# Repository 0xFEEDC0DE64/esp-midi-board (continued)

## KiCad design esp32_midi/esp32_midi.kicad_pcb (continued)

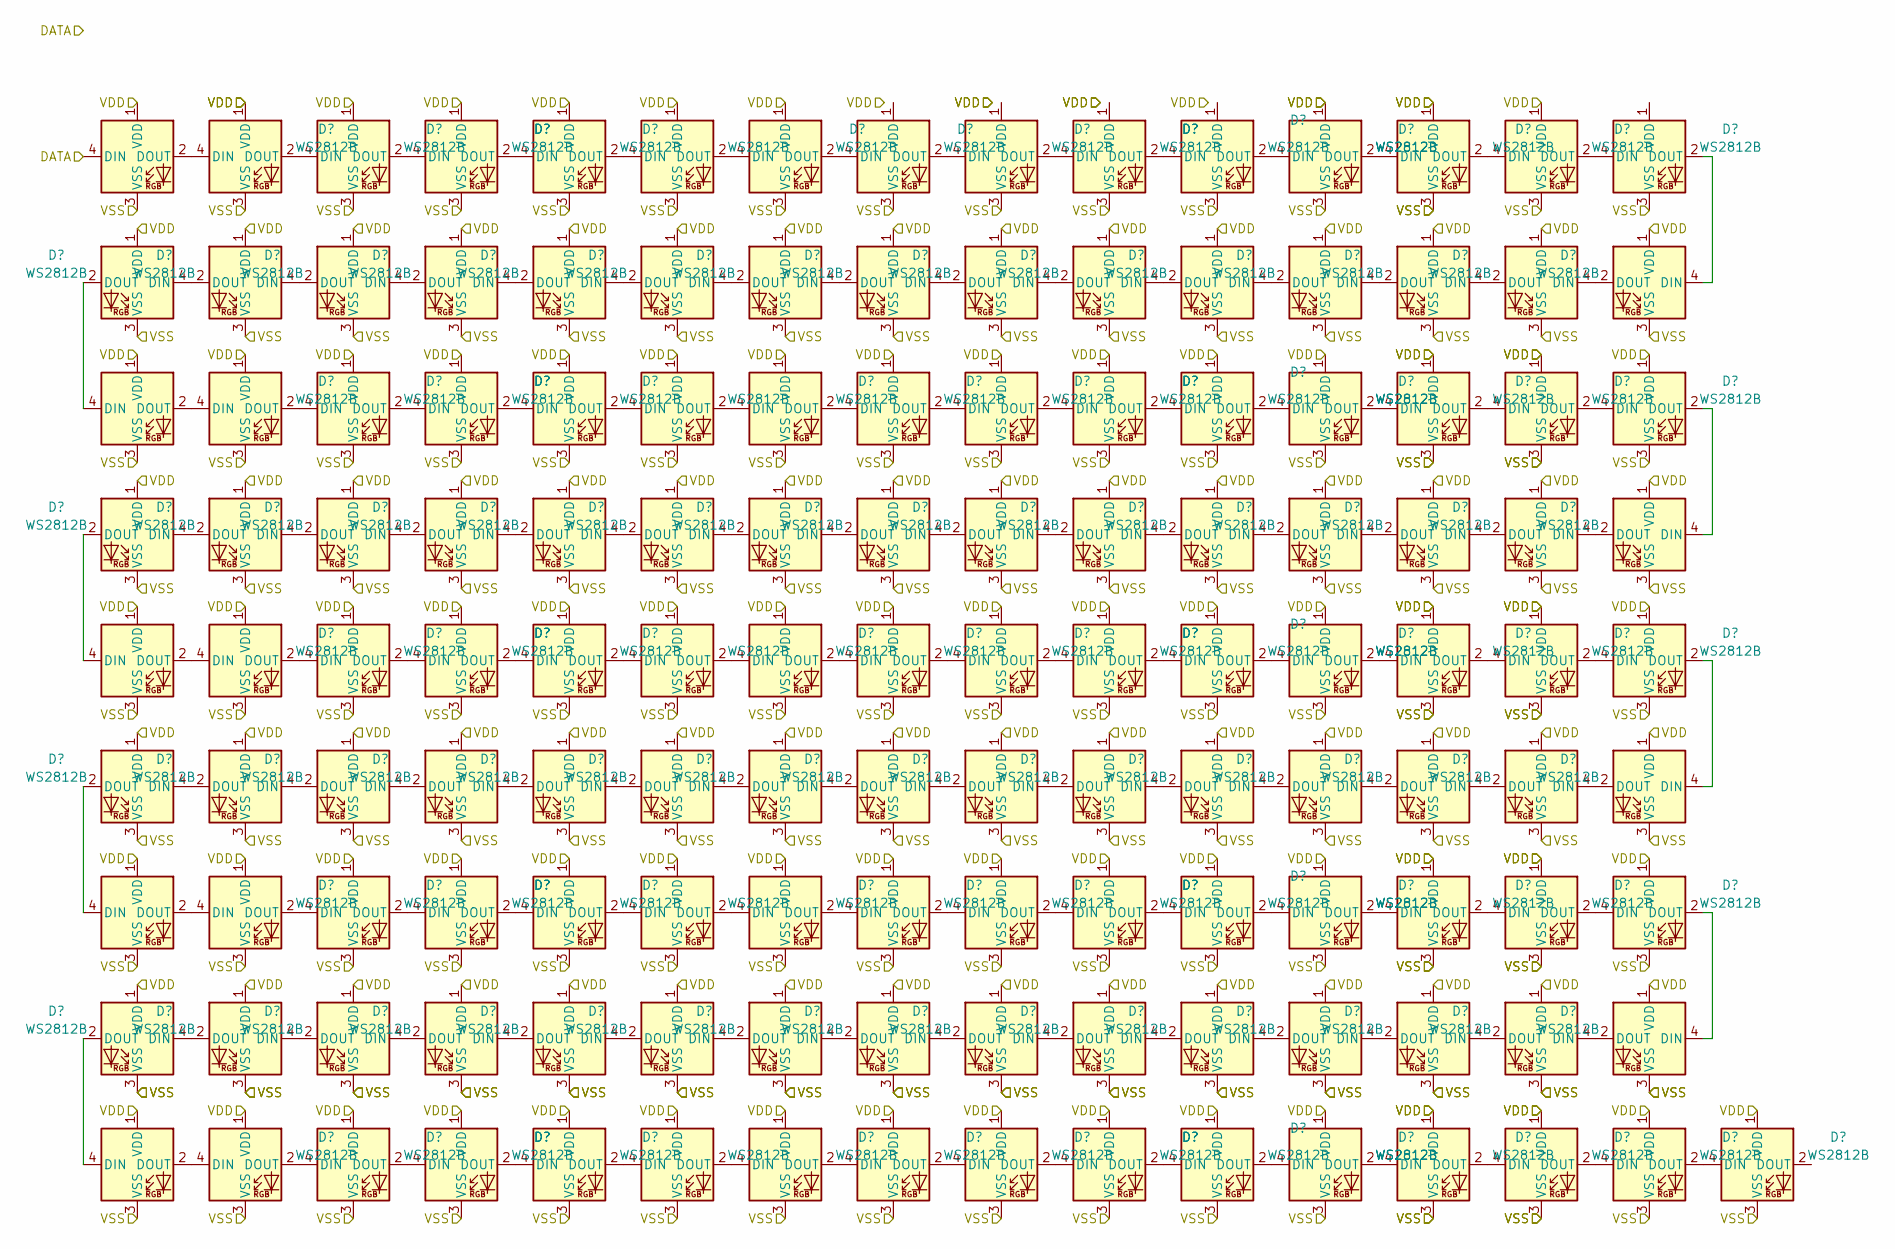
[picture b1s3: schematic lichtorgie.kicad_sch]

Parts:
D101, D102, D103, D104, D105, D106, D107, D108, D109, D110, D111, D112, D113, D114, D115, D116, D117, D118, D119, D120, D121, D122, D123, D124, D125, D126, D127, D128, D129, D130, D131, D132, D133, D134, D135, D136, D137, D138, D139, D140, D141, D142, D143, D144, D145, D146, D147, D148, D149, D150, D151, D152, D153, D154, D155, D156, D157, D158, D159, D160, D161, D162, D163, D164, D165, D166, D167, D168, D169, D170, D171, D172, D173, D174, D175, D176, D177, D178, D179, D180, D181, D182, D183, D184, D185, D186, D187, D188, D189, D190, D191, D192, D193, D194, D195, D196, D197, D198, D199, D200, D201, D202, D203, D204, D205, D206, D207, D208, D209, D210, D211, D212, D213, D214, D215, D216, D217, D218, D219, D220, D221, D222, D223, D224, D225, D226, D227, D228, D229, D230, D231, D232, D233, D234, D235, D236: WS2812B; LED_WS2812B_PLCC4_5.0x5.0mm_P3.2mm

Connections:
+5V: D101.1 (VDD), D102.1 (VDD), D103.1 (VDD), D104.1 (VDD), D105.1 (VDD), D106.1 (VDD), D107.1 (VDD), D112.1 (VDD), D113.1 (VDD), D114.1 (VDD), D116.1 (VDD), D117.1 (VDD), D118.1 (VDD), D119.1 (VDD), D120.1 (VDD), D121.1 (VDD), D122.1 (VDD), D123.1 (VDD), D124.1 (VDD), D125.1 (VDD), D126.1 (VDD), D127.1 (VDD), D128.1 (VDD), D129.1 (VDD), D130.1 (VDD), D131.1 (VDD), D132.1 (VDD), D133.1 (VDD), D134.1 (VDD), D135.1 (VDD), D136.1 (VDD), D137.1 (VDD), D138.1 (VDD), D139.1 (VDD), D140.1 (VDD), D141.1 (VDD), D142.1 (VDD), D143.1 (VDD), D144.1 (VDD), D145.1 (VDD), D146.1 (VDD), D147.1 (VDD), D148.1 (VDD), D149.1 (VDD), D150.1 (VDD), D151.1 (VDD), D152.1 (VDD), D153.1 (VDD), D154.1 (VDD), D155.1 (VDD), D156.1 (VDD), D157.1 (VDD), D158.1 (VDD), D159.1 (VDD), D160.1 (VDD), D161.1 (VDD), D162.1 (VDD), D163.1 (VDD), D164.1 (VDD), D165.1 (VDD), D166.1 (VDD), D167.1 (VDD), D168.1 (VDD), D169.1 (VDD), D170.1 (VDD), D171.1 (VDD), D172.1 (VDD), D173.1 (VDD), D174.1 (VDD), D175.1 (VDD), D176.1 (VDD), D177.1 (VDD), D178.1 (VDD), D179.1 (VDD), D180.1 (VDD), D181.1 (VDD), D182.1 (VDD), D183.1 (VDD), D184.1 (VDD), D185.1 (VDD), D186.1 (VDD), D187.1 (VDD), D188.1 (VDD), D189.1 (VDD), D190.1 (VDD), D191.1 (VDD), D192.1 (VDD), D193.1 (VDD), D194.1 (VDD), D195.1 (VDD), D196.1 (VDD), D197.1 (VDD), D198.1 (VDD), D199.1 (VDD), D200.1 (VDD), D201.1 (VDD), D202.1 (VDD), D203.1 (VDD), D204.1 (VDD), D205.1 (VDD), D206.1 (VDD), D207.1 (VDD), D208.1 (VDD), D209.1 (VDD), D210.1 (VDD), D211.1 (VDD), D212.1 (VDD), D213.1 (VDD), D214.1 (VDD), D215.1 (VDD), D216.1 (VDD), D217.1 (VDD), D218.1 (VDD), D219.1 (VDD), D220.1 (VDD), D221.1 (VDD), D222.1 (VDD), D223.1 (VDD), D224.1 (VDD), D225.1 (VDD), D226.1 (VDD), D227.1 (VDD), D228.1 (VDD), D229.1 (VDD), D230.1 (VDD), D231.1 (VDD), D232.1 (VDD), D233.1 (VDD), D234.1 (VDD), D235.1 (VDD), D236.1 (VDD); also elsewhere on the board
/lichtorgie/DATA: D101.4 (DIN); also elsewhere on the board
GND: D101.3 (VSS), D102.3 (VSS), D103.3 (VSS), D104.3 (VSS), D105.3 (VSS), D106.3 (VSS), D107.3 (VSS), D108.3 (VSS), D109.3 (VSS), D110.3 (VSS), D111.3 (VSS), D112.3 (VSS), D113.3 (VSS), D114.3 (VSS), D115.3 (VSS), D116.3 (VSS), D117.3 (VSS), D118.3 (VSS), D119.3 (VSS), D120.3 (VSS), D121.3 (VSS), D122.3 (VSS), D123.3 (VSS), D124.3 (VSS), D125.3 (VSS), D126.3 (VSS), D127.3 (VSS), D128.3 (VSS), D129.3 (VSS), D130.3 (VSS), D131.3 (VSS), D132.3 (VSS), D133.3 (VSS), D134.3 (VSS), D135.3 (VSS), D136.3 (VSS), D137.3 (VSS), D138.3 (VSS), D139.3 (VSS), D140.3 (VSS), D141.3 (VSS), D142.3 (VSS), D143.3 (VSS), D144.3 (VSS), D145.3 (VSS), D146.3 (VSS), D147.3 (VSS), D148.3 (VSS), D149.3 (VSS), D150.3 (VSS), D151.3 (VSS), D152.3 (VSS), D153.3 (VSS), D154.3 (VSS), D155.3 (VSS), D156.3 (VSS), D157.3 (VSS), D158.3 (VSS), D159.3 (VSS), D160.3 (VSS), D161.3 (VSS), D162.3 (VSS), D163.3 (VSS), D164.3 (VSS), D165.3 (VSS), D166.3 (VSS), D167.3 (VSS), D168.3 (VSS), D169.3 (VSS), D170.3 (VSS), D171.3 (VSS), D172.3 (VSS), D173.3 (VSS), D174.3 (VSS), D175.3 (VSS), D176.3 (VSS), D177.3 (VSS), D178.3 (VSS), D179.3 (VSS), D180.3 (VSS), D181.3 (VSS), D182.3 (VSS), D183.3 (VSS), D184.3 (VSS), D185.3 (VSS), D186.3 (VSS), D187.3 (VSS), D188.3 (VSS), D189.3 (VSS), D190.3 (VSS), D191.3 (VSS), D192.3 (VSS), D193.3 (VSS), D194.3 (VSS), D195.3 (VSS), D196.3 (VSS), D197.3 (VSS), D198.3 (VSS), D199.3 (VSS), D200.3 (VSS), D201.3 (VSS), D202.3 (VSS), D203.3 (VSS), D204.3 (VSS), D205.3 (VSS), D206.3 (VSS), D207.3 (VSS), D208.3 (VSS), D209.3 (VSS), D210.3 (VSS), D211.3 (VSS), D212.3 (VSS), D213.3 (VSS), D214.3 (VSS), D215.3 (VSS), D216.3 (VSS), D217.3 (VSS), D218.3 (VSS), D219.3 (VSS), D220.3 (VSS), D221.3 (VSS), D222.3 (VSS), D223.3 (VSS), D224.3 (VSS), D225.3 (VSS), D226.3 (VSS), D227.3 (VSS), D228.3 (VSS), D229.3 (VSS), D230.3 (VSS), D231.3 (VSS), D232.3 (VSS), D233.3 (VSS), D234.3 (VSS), D235.3 (VSS), D236.3 (VSS); also elsewhere on the board
unnamed: D101.2 (DOUT), D102.4 (DIN)
unnamed: D102.2 (DOUT), D103.4 (DIN)
unnamed: D103.2 (DOUT), D104.4 (DIN)
unnamed: D104.2 (DOUT), D105.4 (DIN)
unnamed: D105.2 (DOUT), D106.4 (DIN)
unnamed: D106.2 (DOUT), D107.4 (DIN)
unnamed: D107.2 (DOUT), D108.4 (DIN)
unnamed: D108.2 (DOUT), D109.4 (DIN)
unnamed: D109.2 (DOUT), D110.4 (DIN)
unnamed: D110.2 (DOUT), D111.4 (DIN)
unnamed: D111.2 (DOUT), D112.4 (DIN)
unnamed: D112.2 (DOUT), D113.4 (DIN)
unnamed: D113.2 (DOUT), D114.4 (DIN)
unnamed: D114.2 (DOUT), D115.4 (DIN)
unnamed: D115.2 (DOUT), D130.4 (DIN)
unnamed: D116.4 (DIN), D117.2 (DOUT)
unnamed: D116.2 (DOUT), D131.4 (DIN)
unnamed: D117.4 (DIN), D118.2 (DOUT)
unnamed: D118.4 (DIN), D119.2 (DOUT)
unnamed: D119.4 (DIN), D120.2 (DOUT)
unnamed: D120.4 (DIN), D121.2 (DOUT)
unnamed: D121.4 (DIN), D122.2 (DOUT)
unnamed: D122.4 (DIN), D123.2 (DOUT)
unnamed: D123.4 (DIN), D124.2 (DOUT)
unnamed: D124.4 (DIN), D125.2 (DOUT)
unnamed: D125.4 (DIN), D126.2 (DOUT)
unnamed: D126.4 (DIN), D127.2 (DOUT)
unnamed: D127.4 (DIN), D128.2 (DOUT)
unnamed: D128.4 (DIN), D129.2 (DOUT)
unnamed: D129.4 (DIN), D130.2 (DOUT)
unnamed: D131.2 (DOUT), D132.4 (DIN)
unnamed: D132.2 (DOUT), D133.4 (DIN)
unnamed: D133.2 (DOUT), D134.4 (DIN)
unnamed: D134.2 (DOUT), D135.4 (DIN)
unnamed: D135.2 (DOUT), D136.4 (DIN)
unnamed: D136.2 (DOUT), D137.4 (DIN)
unnamed: D137.2 (DOUT), D138.4 (DIN)
unnamed: D138.2 (DOUT), D139.4 (DIN)
unnamed: D139.2 (DOUT), D140.4 (DIN)
unnamed: D140.2 (DOUT), D141.4 (DIN)
unnamed: D141.2 (DOUT), D142.4 (DIN)
unnamed: D142.2 (DOUT), D143.4 (DIN)
unnamed: D143.2 (DOUT), D144.4 (DIN)
unnamed: D144.2 (DOUT), D145.4 (DIN)
unnamed: D145.2 (DOUT), D160.4 (DIN)
unnamed: D146.4 (DIN), D147.2 (DOUT)
unnamed: D146.2 (DOUT), D161.4 (DIN)
unnamed: D147.4 (DIN), D148.2 (DOUT)
unnamed: D148.4 (DIN), D149.2 (DOUT)
unnamed: D149.4 (DIN), D150.2 (DOUT)
unnamed: D150.4 (DIN), D151.2 (DOUT)
unnamed: D151.4 (DIN), D152.2 (DOUT)
unnamed: D152.4 (DIN), D153.2 (DOUT)
unnamed: D153.4 (DIN), D154.2 (DOUT)
unnamed: D154.4 (DIN), D155.2 (DOUT)
unnamed: D155.4 (DIN), D156.2 (DOUT)
unnamed: D156.4 (DIN), D157.2 (DOUT)
unnamed: D157.4 (DIN), D158.2 (DOUT)
unnamed: D158.4 (DIN), D159.2 (DOUT)
unnamed: D159.4 (DIN), D160.2 (DOUT)
unnamed: D161.2 (DOUT), D162.4 (DIN)
unnamed: D162.2 (DOUT), D163.4 (DIN)
unnamed: D163.2 (DOUT), D164.4 (DIN)
unnamed: D164.2 (DOUT), D165.4 (DIN)
unnamed: D165.2 (DOUT), D166.4 (DIN)
unnamed: D166.2 (DOUT), D167.4 (DIN)
unnamed: D167.2 (DOUT), D168.4 (DIN)
unnamed: D168.2 (DOUT), D169.4 (DIN)
unnamed: D169.2 (DOUT), D170.4 (DIN)
unnamed: D170.2 (DOUT), D171.4 (DIN)
unnamed: D171.2 (DOUT), D172.4 (DIN)
unnamed: D172.2 (DOUT), D173.4 (DIN)
unnamed: D173.2 (DOUT), D174.4 (DIN)
unnamed: D174.2 (DOUT), D175.4 (DIN)
unnamed: D175.2 (DOUT), D190.4 (DIN)
unnamed: D176.4 (DIN), D177.2 (DOUT)
unnamed: D176.2 (DOUT), D191.4 (DIN)
unnamed: D177.4 (DIN), D178.2 (DOUT)
unnamed: D178.4 (DIN), D179.2 (DOUT)
unnamed: D179.4 (DIN), D180.2 (DOUT)
unnamed: D180.4 (DIN), D181.2 (DOUT)
unnamed: D181.4 (DIN), D182.2 (DOUT)
unnamed: D182.4 (DIN), D183.2 (DOUT)
unnamed: D183.4 (DIN), D184.2 (DOUT)
unnamed: D184.4 (DIN), D185.2 (DOUT)
unnamed: D185.4 (DIN), D186.2 (DOUT)
unnamed: D186.4 (DIN), D187.2 (DOUT)
unnamed: D187.4 (DIN), D188.2 (DOUT)
unnamed: D188.4 (DIN), D189.2 (DOUT)
unnamed: D189.4 (DIN), D190.2 (DOUT)
unnamed: D191.2 (DOUT), D192.4 (DIN)
unnamed: D192.2 (DOUT), D193.4 (DIN)
unnamed: D193.2 (DOUT), D194.4 (DIN)
unnamed: D194.2 (DOUT), D195.4 (DIN)
unnamed: D195.2 (DOUT), D196.4 (DIN)
unnamed: D196.2 (DOUT), D197.4 (DIN)
unnamed: D197.2 (DOUT), D198.4 (DIN)
unnamed: D198.2 (DOUT), D199.4 (DIN)
unnamed: D199.2 (DOUT), D200.4 (DIN)
unnamed: D200.2 (DOUT), D201.4 (DIN)
unnamed: D201.2 (DOUT), D202.4 (DIN)
unnamed: D202.2 (DOUT), D203.4 (DIN)
unnamed: D203.2 (DOUT), D204.4 (DIN)
unnamed: D204.2 (DOUT), D205.4 (DIN)
unnamed: D205.2 (DOUT), D220.4 (DIN)
unnamed: D206.4 (DIN), D207.2 (DOUT)
unnamed: D206.2 (DOUT), D221.4 (DIN)
unnamed: D207.4 (DIN), D208.2 (DOUT)
unnamed: D208.4 (DIN), D209.2 (DOUT)
unnamed: D209.4 (DIN), D210.2 (DOUT)
unnamed: D210.4 (DIN), D211.2 (DOUT)
unnamed: D211.4 (DIN), D212.2 (DOUT)
unnamed: D212.4 (DIN), D213.2 (DOUT)
unnamed: D213.4 (DIN), D214.2 (DOUT)
unnamed: D214.4 (DIN), D215.2 (DOUT)
unnamed: D215.4 (DIN), D216.2 (DOUT)
unnamed: D216.4 (DIN), D217.2 (DOUT)
unnamed: D217.4 (DIN), D218.2 (DOUT)
unnamed: D218.4 (DIN), D219.2 (DOUT)
unnamed: D219.4 (DIN), D220.2 (DOUT)
unnamed: D221.2 (DOUT), D222.4 (DIN)
unnamed: D222.2 (DOUT), D223.4 (DIN)
unnamed: D223.2 (DOUT), D224.4 (DIN)
unnamed: D224.2 (DOUT), D225.4 (DIN)
unnamed: D225.2 (DOUT), D226.4 (DIN)
unnamed: D226.2 (DOUT), D227.4 (DIN)
unnamed: D227.2 (DOUT), D228.4 (DIN)
unnamed: D228.2 (DOUT), D229.4 (DIN)
unnamed: D229.2 (DOUT), D230.4 (DIN)
unnamed: D230.2 (DOUT), D231.4 (DIN)
unnamed: D231.2 (DOUT), D232.4 (DIN)
unnamed: D232.2 (DOUT), D233.4 (DIN)
unnamed: D233.2 (DOUT), D234.4 (DIN)
unnamed: D234.2 (DOUT), D235.4 (DIN)
unnamed: D235.2 (DOUT), D236.4 (DIN)

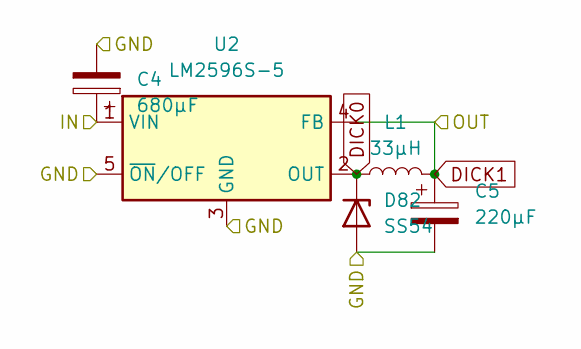
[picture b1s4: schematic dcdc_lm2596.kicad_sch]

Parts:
C4: 680µF; CP_Elec_10x10
C5: 220µF; CP_Elec_10x10
D82: SS54; D_SMA
L1: 33µH; L_10.4x10.4_H4.8
U2: LM2596S-5; TO-263-5_TabPin3

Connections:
+12V: C4.1, U2.1 (VIN); also elsewhere on the board
DICK0: D82.1 (K), L1.1, U2.2 (OUT)
DICK1: C5.1, L1.2, U2.4 (FB); also elsewhere on the board
GND: C4.2, C5.2, D82.2 (A), U2.3 (GND), U2.5 (~ON/OFF); also elsewhere on the board

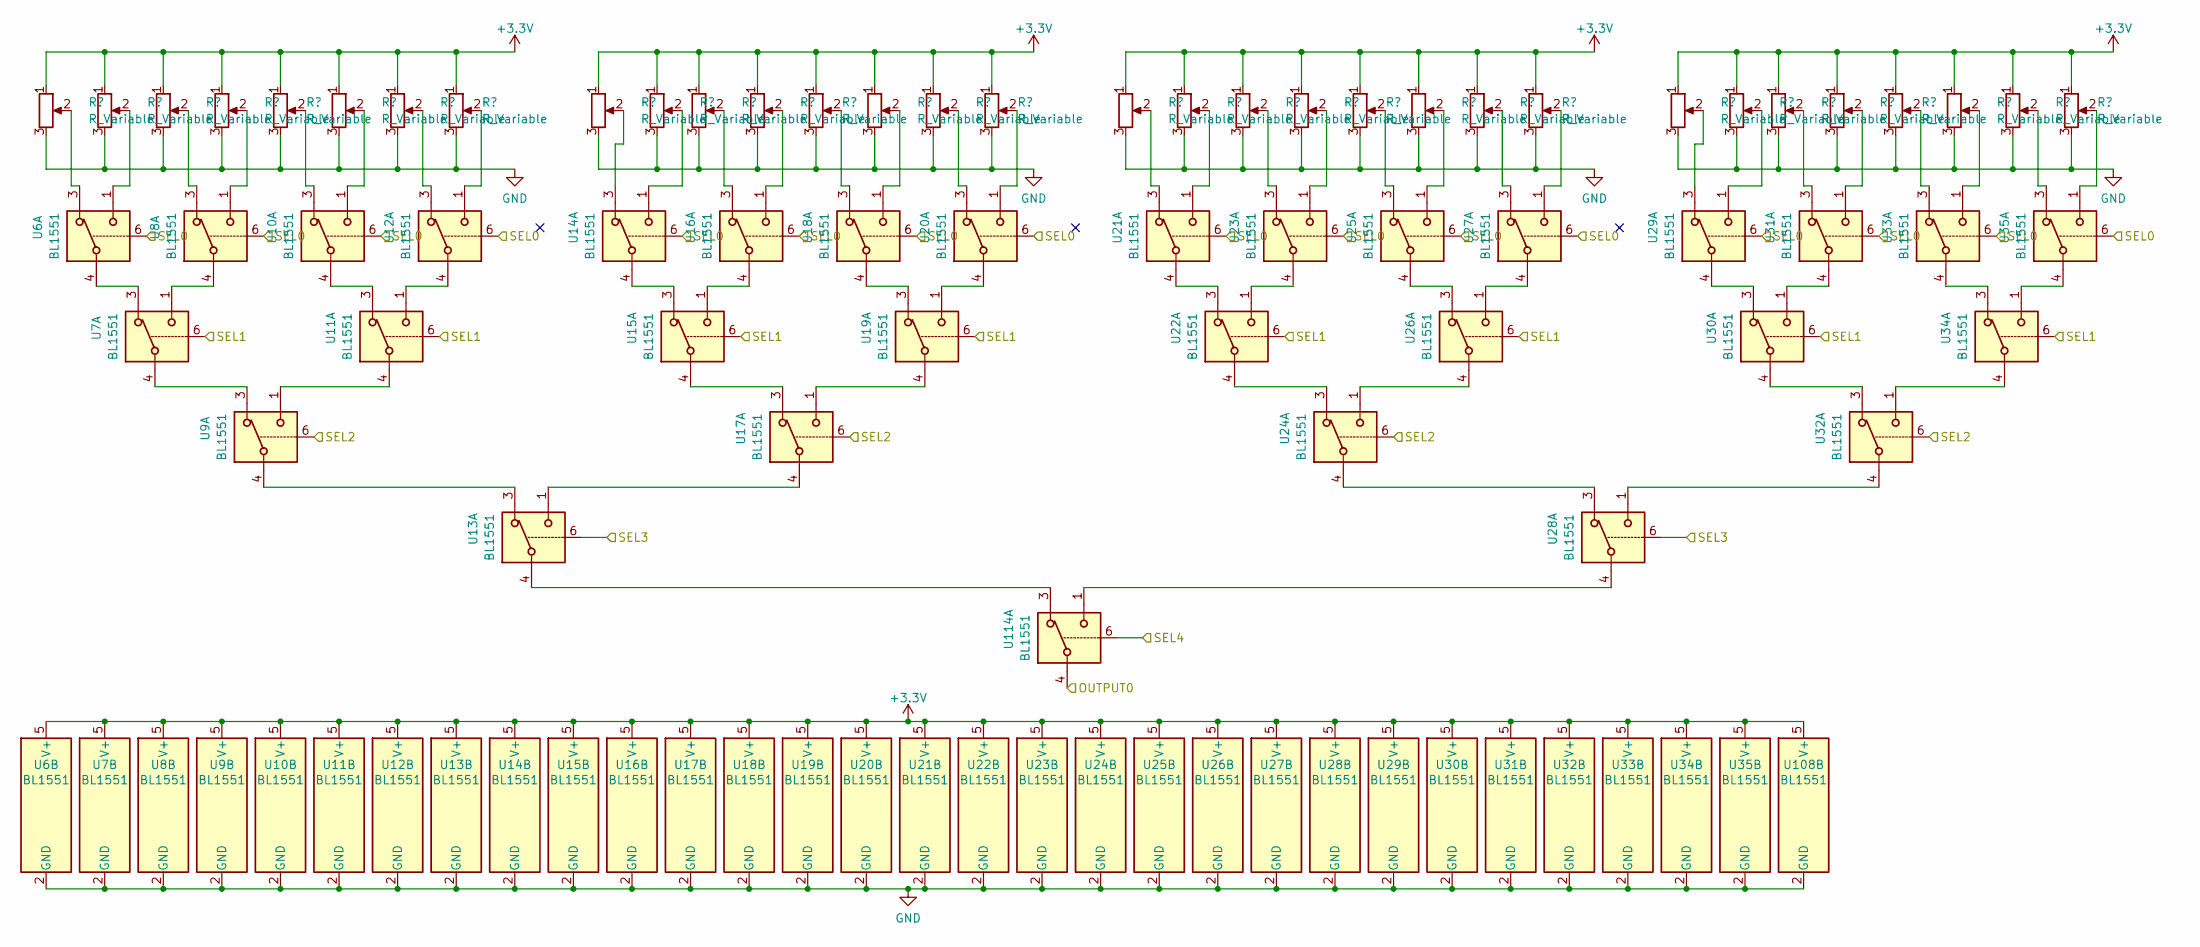
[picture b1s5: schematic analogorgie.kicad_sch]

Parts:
R16, R17, R18, R19, R20, R21, R22, R23: R_Variable; scheißfader
R24, R25, R26, R27, R28, R29, R30, R31, R32, R33, R34, R35, R36, R37, R38, R39, R40, R41, R42, R43, R44, R45, R46, R47: R_Variable; Potentiometer_vom_markt
U6, U7, U8, U9, U10, U11, U12, U13, U14, U15, U16, U17, U18, U19, U20, U21, U22, U23, U24, U25, U26, U27, U28, U29, U30, U31, U32, U33, U34, U35, U108, U114: BL1551; SOT-363_SC-70-6

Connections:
+3.3V: R16.1, R17.1, R18.1, R19.1, R20.1, R21.1, R22.1, R23.1, R24.1, R25.1, R26.1, R27.1, R28.1, R29.1, R30.1, R31.1, R32.1, R33.1, R34.1, R35.1, R36.1, R37.1, R38.1, R39.1, R40.1, R41.1, R42.1, R43.1, R44.1, R45.1, R46.1, R47.1, U6.5 (V+), U7.5 (V+), U8.5 (V+), U9.5 (V+), U10.5 (V+), U11.5 (V+), U12.5 (V+), U13.5 (V+), U14.5 (V+), U15.5 (V+), U16.5 (V+), U17.5 (V+), U18.5 (V+), U19.5 (V+), U20.5 (V+), U21.5 (V+), U22.5 (V+), U23.5 (V+), U24.5 (V+), U25.5 (V+), U26.5 (V+), U27.5 (V+), U28.5 (V+), U29.5 (V+), U30.5 (V+), U31.5 (V+), U32.5 (V+), U33.5 (V+), U34.5 (V+), U35.5 (V+), U108.5 (V+); also elsewhere on the board
/analogorgie/OUTPUT0: U114.4
/analogorgie/SEL0: U6.6, U8.6, U10.6, U12.6, U14.6, U16.6, U18.6, U20.6, U21.6, U23.6, U25.6, U27.6, U29.6, U31.6, U33.6, U35.6; also elsewhere on the board
/analogorgie/SEL1: U7.6, U11.6, U15.6, U19.6, U22.6, U26.6, U30.6, U34.6; also elsewhere on the board
/analogorgie/SEL2: U9.6, U17.6, U24.6, U32.6; also elsewhere on the board
/analogorgie/SEL3: U13.6, U28.6; also elsewhere on the board
/analogorgie/SEL4: U114.6; also elsewhere on the board
GND: R16.3, R17.3, R18.3, R19.3, R20.3, R21.3, R22.3, R23.3, R24.3, R25.3, R26.3, R27.3, R28.3, R29.3, R30.3, R31.3, R32.3, R33.3, R34.3, R35.3, R36.3, R37.3, R38.3, R39.3, R40.3, R41.3, R42.3, R43.3, R44.3, R45.3, R46.3, R47.3, U6.2 (GND), U7.2 (GND), U8.2 (GND), U9.2 (GND), U10.2 (GND), U11.2 (GND), U12.2 (GND), U13.2 (GND), U14.2 (GND), U15.2 (GND), U16.2 (GND), U17.2 (GND), U18.2 (GND), U19.2 (GND), U20.2 (GND), U21.2 (GND), U22.2 (GND), U23.2 (GND), U24.2 (GND), U25.2 (GND), U26.2 (GND), U27.2 (GND), U28.2 (GND), U29.2 (GND), U30.2 (GND), U31.2 (GND), U32.2 (GND), U33.2 (GND), U34.2 (GND), U35.2 (GND), U108.2 (GND); also elsewhere on the board
unnamed: R16.2, U6.3
unnamed: R17.2, U6.1
unnamed: R18.2, U8.3
unnamed: R19.2, U8.1
unnamed: R20.2, U10.3
unnamed: R21.2, U10.1
unnamed: R22.2, U12.3
unnamed: R23.2, U12.1
unnamed: R24.2, U14.3
unnamed: R25.2, U14.1
unnamed: R26.2, U16.3
unnamed: R27.2, U16.1
unnamed: R28.2, U18.3
unnamed: R29.2, U18.1
unnamed: R30.2, U20.3
unnamed: R31.2, U20.1
unnamed: R32.2, U21.3
unnamed: R33.2, U21.1
unnamed: R34.2, U23.3
unnamed: R35.2, U23.1
unnamed: R36.2, U25.3
unnamed: R37.2, U25.1
unnamed: R38.2, U27.3
unnamed: R39.2, U27.1
unnamed: R40.2, U29.3
unnamed: R41.2, U29.1
unnamed: R42.2, U31.3
unnamed: R43.2, U31.1
unnamed: R44.2, U33.3
unnamed: R45.2, U33.1
unnamed: R46.2, U35.3
unnamed: R47.2, U35.1
unnamed: U6.4, U7.3
unnamed: U7.1, U8.4
unnamed: U7.4, U9.3
unnamed: U10.4, U11.3
unnamed: U11.1, U12.4
unnamed: U9.1, U11.4
unnamed: U13.1, U17.4
unnamed: U9.4, U13.3
unnamed: U14.4, U15.3
unnamed: U15.1, U16.4
unnamed: U15.4, U17.3
unnamed: U17.1, U19.4
unnamed: U18.4, U19.3
unnamed: U19.1, U20.4
unnamed: U21.4, U22.3
unnamed: U22.1, U23.4
unnamed: U22.4, U24.3
unnamed: U24.1, U26.4
unnamed: U24.4, U28.3
unnamed: U25.4, U26.3
unnamed: U26.1, U27.4
unnamed: U28.1, U32.4
unnamed: U29.4, U30.3
unnamed: U30.1, U31.4
unnamed: U30.4, U32.3
unnamed: U32.1, U34.4
unnamed: U33.4, U34.3
unnamed: U34.1, U35.4
unnamed: U28.4, U114.1
unnamed: U13.4, U114.3

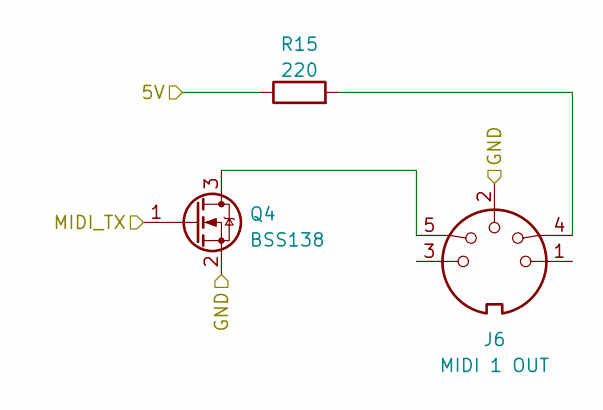
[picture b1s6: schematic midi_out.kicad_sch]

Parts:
J6: MIDI 1 OUT; scheißmidi
Q4: BSS138; SOT-23
R15: 220; R_1206_3216Metric

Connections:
+5V: R15.1; also elsewhere on the board
/MIDI IN THRU OUT/RX: Q4.1 (G); also elsewhere on the board
GND: J6.2, Q4.2 (S); also elsewhere on the board
unnamed: J6.4, R15.2
unnamed: J6.5, Q4.3 (D)

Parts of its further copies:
J4: MIDI 1 OUT; scheißmidi
Q1: BSS138; SOT-23
R2: 220; R_1206_3216Metric

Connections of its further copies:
+5V: R2.1; also elsewhere on the board
/MIDI IN THRU OUT/TX: Q1.1 (G); also elsewhere on the board
GND: J4.2, Q1.2 (S); also elsewhere on the board
unnamed: J4.4, R2.2
unnamed: J4.5, Q1.3 (D)

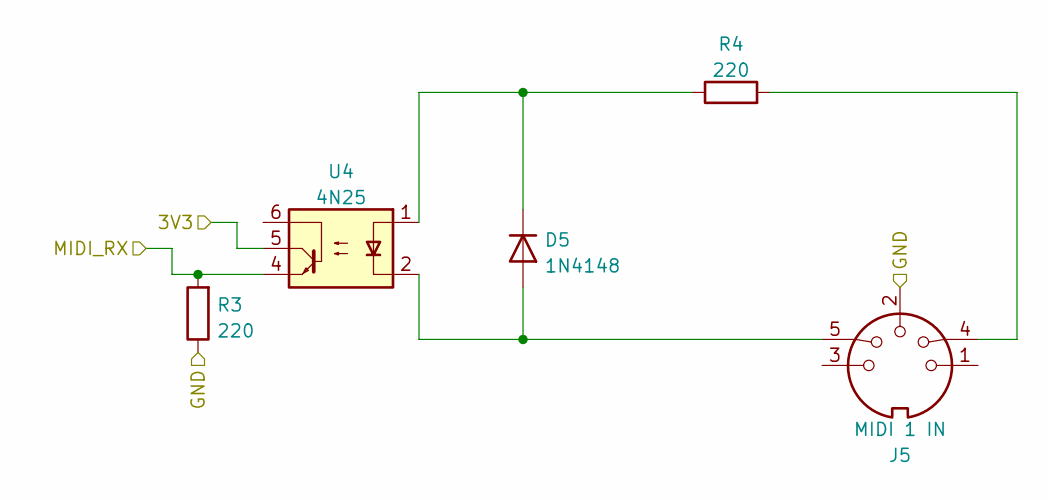
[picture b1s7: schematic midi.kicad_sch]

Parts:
D5: 1N4148; D_SOD-123
J5: MIDI 1 IN; scheißmidi
R3, R4: 220; R_1206_3216Metric
U4: 4N25; DIP-6_W7.62mm

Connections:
+3.3V: U4.5; also elsewhere on the board
/MIDI IN THRU OUT/RX: R3.2, U4.4; also elsewhere on the board
GND: J5.2, R3.1; also elsewhere on the board
unnamed: D5.2 (A), J5.5, U4.2
unnamed: D5.1 (K), R4.1, U4.1
unnamed: J5.4, R4.2

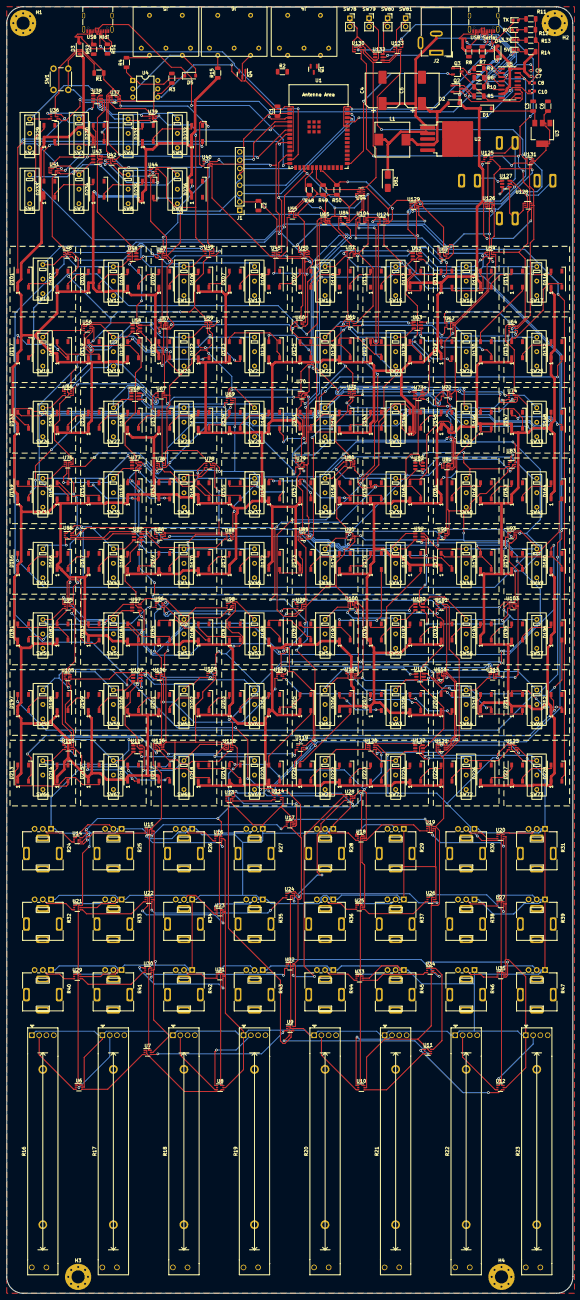
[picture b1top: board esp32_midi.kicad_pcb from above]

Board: 2 copper layers, 172.5 x 392.0 mm, 440 parts (0 on the bottom side), 408 nets.

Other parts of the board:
3.3V: LED; LED_0603_1608Metric
5V: LED5V; LED_0603_1608Metric
C7, C9: 100n; C_0402_1005Metric
C8: 1u; C_0603_1608Metric
C10: 10u; C_0603_1608Metric
NT101: NetTie_3; NetTie-3_SMD_Pad0.5mm
Q2, Q3: SS8050_C2150; TSOT-23
R5, R6: 12k; R_1206_3216Metric
R9, R10: 10k; R_1206_3216Metric
R11, R12, R13, R14: 1k; R_1206_3216Metric
RX: LED; LED_0603_1608Metric
TX: LED; LED_0603_1608Metric
U5: CH343G; SOIC-16_3.9x9.9mm_P1.27mm
USB Midi: MC-311D; USB-C-SMD_MC-311D
USB Serial: MC-311D; USB-C-SMD_MC-311D

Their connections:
5V_USB2: C7.2, NT101.2, R14.1, U5.7 (VBUS), U5.16 (VDD5); also elsewhere on the board
+3V3: C8.2, R9.2, R10.2, R11.1, R12.1, R13.1, U5.15 (VIO); also elsewhere on the board
/flasher/DTR: Q3.3 (C), R5.1, R10.1, U5.10 (~DTR/TNOW)
/flasher/ESP_EN: C10.2, Q2.3 (C); also elsewhere on the board
/flasher/ESP_IO0: Q3.2 (E); also elsewhere on the board
/flasher/RTS: Q2.2 (E), R6.1, U5.11 (~RTS)
/flasher/USB_DN: U5.6 (UD-), USB Serial.A7 (DN1), USB Serial.B7 (DN2)
/flasher/USB_DP: U5.5 (UD+), USB Serial.A6 (DP1), USB Serial.B6 (DP2)
ESP_RX: R9.1, TX.1 (K), U5.2 (TXD); also elsewhere on the board
ESP_TX: RX.1 (K), U5.3 (RXD); also elsewhere on the board
GND: 3.3V.1 (K), 5V.1 (K), C7.1, C8.1, C9.1, C10.1, U5.1 (GND), USB Midi.1 (SHIELD), USB Midi.2 (SHIELD), USB Midi.3 (SHIELD), USB Midi.4 (SHIELD), USB Midi.A1-B12 (GND), USB Midi.B1-A12 (GND), USB Serial.1 (SHIELD), USB Serial.2 (SHIELD), USB Serial.3 (SHIELD), USB Serial.4 (SHIELD), USB Serial.A1-B12 (GND), USB Serial.B1-A12 (GND); also elsewhere on the board
unnamed: R11.2, TX.2 (A)
unnamed: R12.2, RX.2 (A)
unnamed: 3.3V.2 (A), R13.2
unnamed: 5V.2 (A), R14.2
unnamed: Q2.1 (B), R5.2
unnamed: Q3.1 (B), R6.2
unnamed: C9.2, U5.4 (V3)
unnamed 400: USB Serial.A5 (CC1); also elsewhere on the board
unnamed 401: USB Serial.B5 (CC2); also elsewhere on the board
unnamed 402: USB Midi.A5 (CC1); also elsewhere on the board
unnamed 403: USB Midi.B5 (CC2); also elsewhere on the board
THIN_5V_USB0: USB Midi.A4-B9 (VBUS); also elsewhere on the board
THIN_5V_USB1: USB Midi.B4-A9 (VBUS); also elsewhere on the board
THIN_USB_FLASHER_0: NT101.1, USB Serial.A4-B9 (VBUS)
THIN_USB_FLASHER_1: NT101.3, USB Serial.B4-A9 (VBUS)
USB2.0_D+: USB Midi.A6 (DP1), USB Midi.B6 (DP2); also elsewhere on the board
USB2.0_D-: USB Midi.A7 (DN1), USB Midi.B7 (DN2); also elsewhere on the board

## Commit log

2023-02-06 added midi thru
2023-07-16 work in progress, added usb-c flasher, add display connector, add midi connections
2023-07-16 Added analogorgie
2023-07-18 More footprints applied
2023-07-18 Removed other bullshit projects
2023-07-18 Add lights
2023-07-18 Add 64buttons
2023-07-19 Updated pcb
2023-07-21 Add ordentliche-teile
2023-07-21 Started work on PCB
2023-07-21 More PCB implementations
2023-07-22 More pcb
2023-07-22 improve component spacing, add more LEDs
2023-07-22 add GND zone
2023-07-22 Net improvements
2023-07-22 More pcb routings
2023-07-23 muchos viasos
2023-07-23 Finished
2023-07-28 Everything changed
2023-08-03 First load of bug fixes
2023-08-03 Update parts numbers
